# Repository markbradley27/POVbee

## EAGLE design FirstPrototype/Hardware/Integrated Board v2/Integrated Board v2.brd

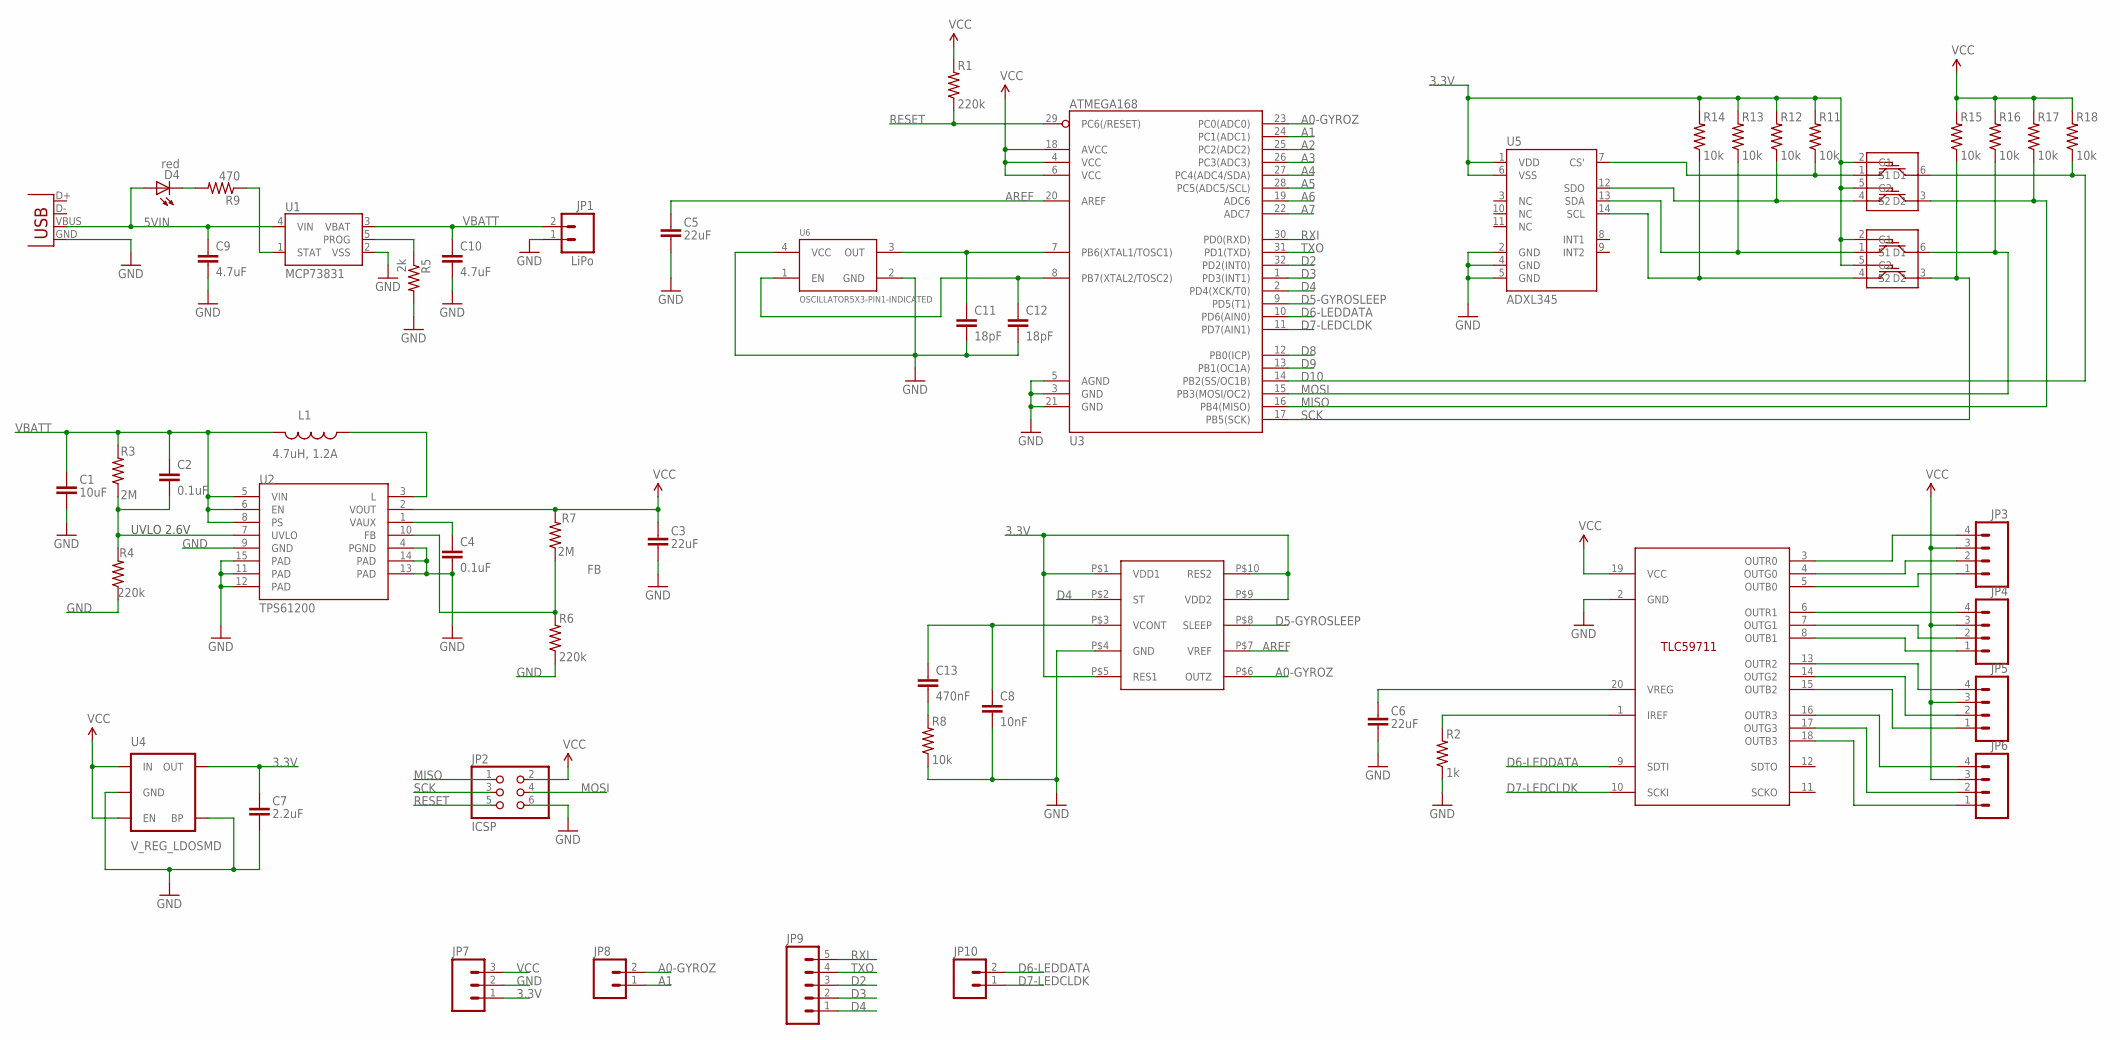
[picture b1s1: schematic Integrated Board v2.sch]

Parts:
C1: 10uF; 0603
C2, C4: 0.1uF; 0603-CAP
C3, C5, C6: 22uF; 0805
C7: 2.2uF; 0603
C8: 10nF; 0603-CAP
C9, C10: 4.7uF; 0603-CAP
C11, C12: 18pF; 0603-CAP
C13: 470nF; 0603-CAP
D4: red; LED-0603
JP1: LiPo; JST-2-SMD
JP2: ICSP; 2X03
JP3, JP4, JP5, JP6: M04PTH; 1X04
JP7: M03PTH; 1X03
JP8, JP10: M02PTH; 1X02
JP9: M05PTH; 1X05
L1: 4.7uH, 1.2A; CDRH2D09
R1, R4, R6: 220k; 0603-RES
R2: 1k; 0603-RES
R3, R7: 2M; 0603-RES
R5: 2k; 0603-RES
R8, R11, R12, R13, R14, R15, R16, R17, R18: 10k; 0603-RES
R9: 470; 0603-RES
U1: MCP73831; SOT23-5
U2: TPS61200; QFN-10_PAD
U3: ATMEGA168; TQFP32-08
U4: V_REG_LDOSMD; SOT23-5
U5: ADXL345; LGA14
U6: OSCILLATOR5X3-PIN1-INDICATED; CRYSTAL-OSC-SMD-5X3
U$1: TLC59711; TSSOP20
U$2, U$3: 2N7002DW; SOT363
U$4: LY3100ALH; LGA10
X1: USB-MICROB

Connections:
3.3V: C7.1, JP7.1, R11.2, R12.2, R13.2, R14.2, U4.5 (OUT), U5.1 (VDD), U5.6 (VSS), U$2.2 (G1), U$2.5 (G2), U$3.2 (G1), U$3.5 (G2), U$4.P$1 (VDD1), U$4.P$5 (RES1), U$4.P$9 (VDD2), U$4.P$10 (RES2)
5VIN: C9.1, D4.A, U1.4 (VIN), X1.VBUS
A0-GYROZ: JP8.2, U3.23 (PC0(ADC0)), U$4.P$6 (OUTZ)
A1: JP8.1, U3.24 (PC1(ADC1))
A2: U3.25 (PC2(ADC2))
A3: U3.26 (PC3(ADC3))
A4: U3.27 (PC4(ADC4/SDA))
A5: U3.28 (PC5(ADC5/SCL))
A6: U3.19 (ADC6)
A7: U3.22 (ADC7)
AREF: C5.1, U3.20 (AREF), U$4.P$7 (VREF)
D2: JP9.3, U3.32 (PD2(INT0))
D3: JP9.2, U3.1 (PD3(INT1))
D4: JP9.1, U3.2 (PD4(XCK/T0)), U$4.P$2 (ST)
D5-GYROSLEEP: U3.9 (PD5(T1)), U$4.P$8 (SLEEP)
D6-LEDDATA: JP10.2, U3.10 (PD6(AIN0)), U$1.9 (SDTI)
D7-LEDCLDK: JP10.1, U3.11 (PD7(AIN1)), U$1.10 (SCKI)
D8: U3.12 (PB0(ICP))
D9: U3.13 (PB1(OC1A))
D10: R18.1, U3.14 (PB2(SS/OC1B)), U$2.6 (D1)
FB: R6.2, R7.1, U2.10 (FB)
GND: C1.2, C3.2, C4.2, C5.2, C6.2, C7.2, C8.2, C9.2, C10.2, C11.2, C12.2, JP1.1, JP2.6, JP7.2, R2.1, R4.1, R5.2, R6.1, R8.1, U1.2 (VSS), U2.4 (PGND), U2.9 (GND), U2.11 (PAD), U2.12 (PAD), U2.13 (PAD), U2.14 (PAD), U2.15 (PAD), U3.3 (GND), U3.5 (AGND), U3.21 (GND), U4.2 (GND), U4.4 (BP), U5.2 (GND), U5.4 (GND), U5.5 (GND), U6.2 (GND), U6.4 (VCC), U$1.2 (GND), U$4.P$4 (GND), X1.GND
MISO: JP2.1, R17.1, U3.16 (PB4(MISO)), U$2.3 (D2)
MOSI: JP2.4, R16.1, U3.15 (PB3(MOSI/OC2)), U$3.6 (D1)
unnamed: C4.1, U2.1 (VAUX)
unnamed: L1.P$1 (1), U2.3 (L)
unnamed: C11.1, U3.7 (PB6(XTAL1/TOSC1)), U6.3 (OUT)
unnamed: C13.2, R8.2
unnamed: C6.1, U$1.20 (VREG)
unnamed: R2.2, U$1.1 (IREF)
unnamed: D4.C, R9.2
unnamed: R11.1, U5.7 (CS'), U$2.1 (S1)
unnamed: R5.1, U1.5 (PROG)
unnamed: R12.1, U5.12 (SDO), U$2.4 (S2)
unnamed: R13.1, U5.13 (SDA), U$3.1 (S1)
unnamed: R9.1, U1.1 (STAT)
unnamed: R14.1, U5.14 (SCL), U$3.4 (S2)
unnamed: JP4.4 (B), U$1.6 (OUTR1)
unnamed: JP4.2 (R), U$1.7 (OUTG1)
unnamed: JP4.1 (COM), U$1.8 (OUTB1)
unnamed: JP5.4 (B), U$1.13 (OUTR2)
unnamed: JP5.2 (R), U$1.14 (OUTG2)
unnamed: JP5.1 (COM), U$1.15 (OUTB2)
unnamed: JP6.4 (B), U$1.16 (OUTR3)
unnamed: JP6.2 (R), U$1.17 (OUTG3)
unnamed: JP6.1 (COM), U$1.18 (OUTB3)
unnamed: JP3.1 (COM), U$1.5 (OUTB0)
unnamed: JP3.2 (R), U$1.4 (OUTG0)
unnamed: JP3.4 (B), U$1.3 (OUTR0)
unnamed: C12.1, U3.8 (PB7(XTAL2/TOSC2)), U6.1 (EN)
unnamed: C8.1, C13.1, U$4.P$3 (VCONT)
RESET: JP2.5, R1.1, U3.29 (PC6(/RESET))
RXI: JP9.5, U3.30 (PD0(RXD))
SCK: JP2.3, R15.1, U3.17 (PB5(SCK)), U$3.3 (D2)
TXO: JP9.4, U3.31 (PD1(TXD))
UVLO: C2.2, R3.1, R4.2, U2.7 (UVLO)
VBATT: C1.1, C2.1, C10.1, JP1.2, L1.P$2 (2), R3.2, U1.3 (VBAT), U2.5 (VIN), U2.6 (EN), U2.8 (PS)
VCC: C3.1, JP2.2, JP3.3 (G), JP4.3 (G), JP5.3 (G), JP6.3 (G), JP7.3, R1.2, R7.2, R15.2, R16.2, R17.2, R18.2, U2.2 (VOUT), U3.4 (VCC), U3.6 (VCC), U3.18 (AVCC), U4.1 (IN), U4.3 (EN), U$1.19 (VCC)

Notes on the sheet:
UVLO 2.6V

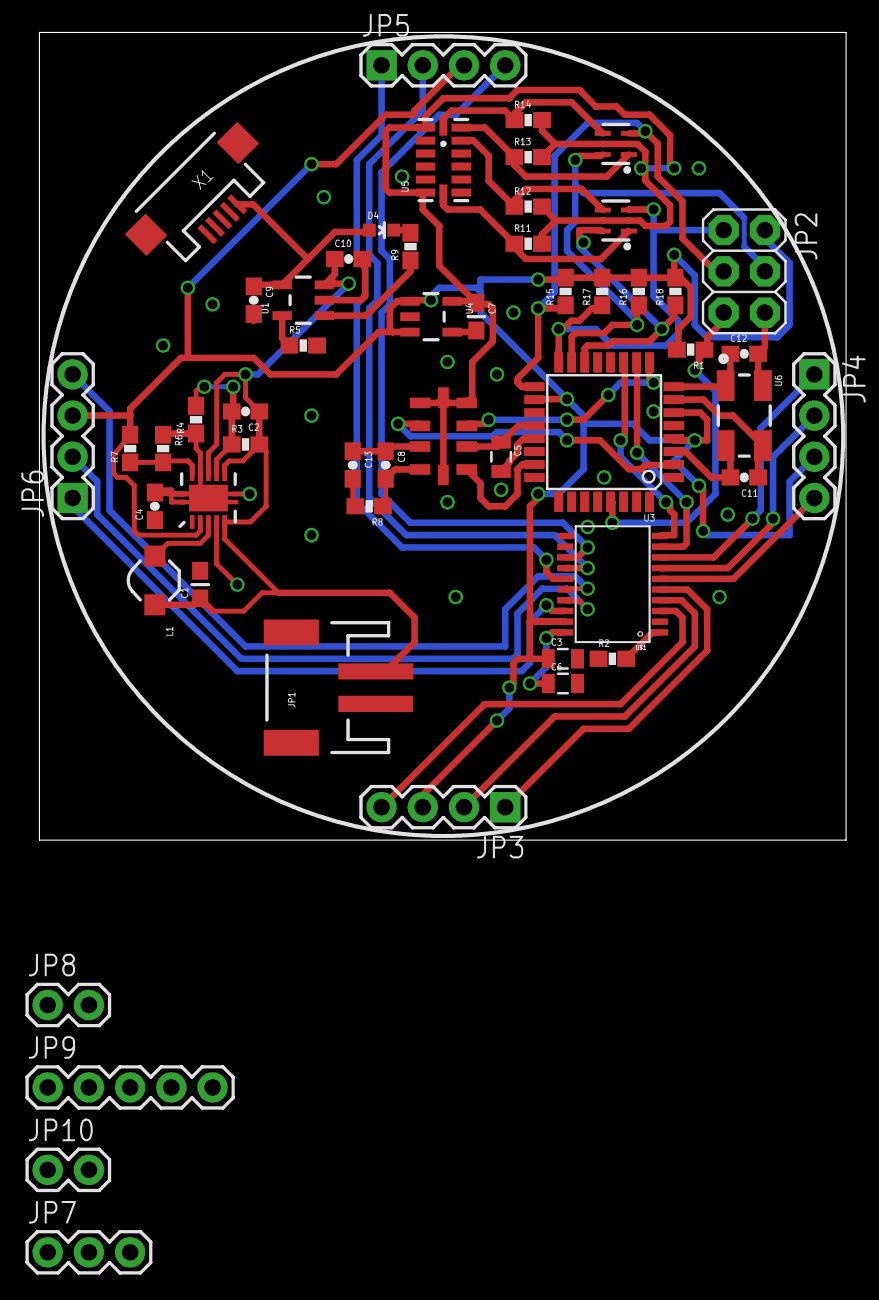
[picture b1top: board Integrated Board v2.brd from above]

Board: 2 copper layers, 49.7 x 49.8 mm, 53 parts (0 on the bottom side), 50 nets.

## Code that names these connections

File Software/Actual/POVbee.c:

/********************************************************************************
Includes
********************************************************************************/
#include <avr/io.h>
#include <avr/interrupt.h>
#include <stdbool.h>
#include <avr/eeprom.h>
#include <stdio.h>
#include <string.h>
#include <avr/pgmspace.h>
#include <avr/interrupt.h>
#include "WS2811.h"
 
/********************************************************************************
Macros and Defines
********************************************************************************/
#define F_CPU 16000000UL
#define BAUD 9600UL
#define MYUBRR F_CPU/16/BAUD-1
DEFINE_WS2811_FN(WS2811RGB, PORTC, 2)
 
/********************************************************************************
Function Prototypes
********************************************************************************/
int16_t get_rotation_gyro(void);
void accel_init(void);
int16_t accel_read_axis(uint8_t);
void port_init(void);
void adc_init(void);
void spim_init(void);
void timer_init(void);
void spi_tx(char data);
uint16_t analog_read(uint8_t channel);
void usart_init( uint16_t ubrr);
void usart_putchar(char data);
char usart_getchar(void);
unsigned char usart_kbhit(void);
void usart_pstr(char *s);
int usart_putchar_printf(char var, FILE *stream);

/********************************************************************************
Global Variables
********************************************************************************/
static FILE mystdout = FDEV_SETUP_STREAM(usart_putchar_printf, NULL, _FDEV_SETUP_WRITE);
RGB_t rgb[4] = {{0, 0, 0}, {0, 0, 0}, {0, 0, 0}, {0, 0, 0}};
uint32_t milis = 0;

/********************************************************************************
Main
********************************************************************************/
int main(void) {
    // AVR init
    port_init();
    adc_init();
    spim_init();
    usart_init(MYUBRR);
    timer_init();
    sei();              // Enable interrupts
    stdout = &mystdout;

    // Device init
    accel_init();

    // Variable declaration
    int16_t rotation = 0;
    int16_t accel_x = 0;
    int16_t accel_y = 0;
    int16_t accel_z = 0;
    uint8_t seconds = 0;

    // Main loop
    while (true) {
        rotation = get_rotation_gyro();
        accel_x = accel_read_axis('x');
        accel_y = accel_read_axis('y');
        accel_z = accel_read_axis('z');

        // Roughly estimate seconds
        if (milis >= 1000) {
            ++seconds;
            milis = 0;
        }

        printf("Rotation: %3d\t", rotation);
        printf("Accel: %3d,\t%3d,\t%3d\t", accel_x, accel_y, accel_z);
        printf("Seconds: %3u\r\n", seconds);

        uint8_t i;
        if (rotation < -15) {
            for (i = 0; i < 4; ++i) {
                rgb[i].g = 255;
                rgb[i].b = 0;
                rgb[i].r = 0;
            }
        }
        else if (rotation > 15) {
            for (i = 0; i < 4; ++i) {
                rgb[i].g = 0;
                rgb[i].b = 255;
                rgb[i].r = 0;
            }
        }
        else {
            for (i = 0; i < 4; ++i) {
                rgb[i].g = 0;
                rgb[i].b = 0;
                rgb[i].r = 255;
            }
        }

        WS2811RGB(rgb, ARRAYLEN(rgb));
    }
}

/********************************************************************************
Device helpers
********************************************************************************/
// Gyro
int16_t get_rotation_gyro(void) {
    return analog_read(7) - analog_read(6);
}

// Accel
void accel_init(void) {
    // Set to standby mode
    PORTB &= ~(1<<PB2);
    spi_tx(0x2D);
    spi_tx(0x00);
    PORTB |= (1<<PB2);

    // Set to measure mode
    PORTB &= ~(1<<PB2);
    spi_tx(0x2D);
    spi_tx(0x08);
    PORTB |= (1<<PB2);

    // Set to +/- 16g, full-resolution
    PORTB &= ~(1<<PB2);
    spi_tx(0x31);
    spi_tx(0x0B);
    PORTB |= (1<<PB2);
}
int16_t accel_read_axis(uint8_t axis) {
    int16_t axis_accel = 0x00;
    switch(axis) {
        case 'x': axis = 0x32; break;
        case 'y': axis = 0x34; break;
        case 'z': axis = 0x36; break;
        default: return 0;
    }

    // Pull CS low
    PORTB &= ~(1<<PB2);

    // Read x data registers
    spi_tx(0x80 | 0x40 | axis);
    spi_tx(0x00);
    axis_accel |= SPDR;
    spi_tx(0x00);
    axis_accel |= SPDR << 8;

    // Drive CS high
    PORTB |= (1<<PB2);

    return axis_accel;
}

// Timer
uint32_t get_micros(void) {
    return (milis * 1000) + ((uint32_t)(TCNT0 - 6) * 4);
}
void timer_reset(void) {
    TCNT0 = 6;
    milis = 0;
}

/********************************************************************************
Device initialization
********************************************************************************/
void port_init(void) {
    // Turn on green light
    PORTC &= ~(1 << PC4);
    DDRC |= (1 << PC4);

    // Gyro pins
    PORTC &= ~(1 << PC0);
    PORTC &= ~(1 << PC1);
    DDRC |= 0x03;

    // Pixel pin
    DDRC |= (1<<PC2);
    PORTC &= ~(1<<PC2);
}

void adc_init(void) {
    ADMUX &= ~0xE0;         // AREF reference voltage, right adjusted result
    ADCSRA = 0x87;          // ADC enabled, no auto-trigger, aclock = sysclock/128
}

void spim_init(void) {
    DDRB = (1<<PB2)|(1<<PB3)|(1<<PB5);     // Set CS, MOSI, and SCK output, all others input
    PORTB |= (1<<PB2);                     // Set CS high initially
    // TODO: Try speeding this back up
    SPCR = (1<<SPE)|(1<<MSTR)|(1<<CPOL)|(1<<CPHA)|(1<<SPR1)|(1<<SPR0);    // Enable SPI, Master, set clock rate fck/128
}

void timer_init(void) {
    TIMSK0 = (1<<TOIE0);            // Enable timer overflow interrupt for timer0
    TCNT0 = 0x00;                   // Set timer0 counter initial value to 0
    TCCR0B = (1<<CS00)|(1<<CS01);   // Start timer0 with 1/64 prescaler
}

/********************************************************************************
Interrupt Service Routines
********************************************************************************/
ISR(TIMER0_OVF_vect) {
    ++milis;
    TCNT0 = 6;
}

/********************************************************************************
ADC Related
********************************************************************************/
uint16_t analog_read(uint8_t channel) {
    ADMUX = (ADMUX & 0xF0) | channel;
    ADCSRA |= 0x40;
    while(!(ADCSRA & 0x10));
    ADCSRA |= 0x10;
    return ADC;
}

/********************************************************************************
SPI Related
********************************************************************************/
void spi_tx(char data) {
    SPDR = data;
    while(!(SPSR & (1<<SPIF)));
}

/********************************************************************************
usart Related
********************************************************************************/
void usart_init( uint16_t ubrr) {
    // Set baud rate
    UBRR0H = (uint8_t)(ubrr>>8);
    UBRR0L = (uint8_t)ubrr;
    // Enable receiver and transmitter
    UCSR0B = (1<<RXEN0)|(1<<TXEN0);
    // Set frame format: 8data, 1stop bit
    //UCSR0C = (1<<URSEL)|(3<<UCSZ0);
    UCSR0C = (3<<UCSZ00);
}
void usart_putchar(char data) {
    // Wait for empty transmit buffer
    while ( !(UCSR0A & (_BV(UDRE0))) );
    // Start transmission
    UDR0 = data; 
}
char usart_getchar(void) {
    // Wait for incoming data
    while ( !(UCSR0A & (_BV(RXC0))) );
    // Return the data
    return UDR0;
}
unsigned char usart_kbhit(void) {
    //return nonzero if char waiting polled version
    unsigned char b;
    b=0;
    if(UCSR0A & (1<<RXC0)) b=1;
    return b;
}
void usart_pstr(char *s) {
    // loop through entire string
    while (*s) { 
        usart_putchar(*s);
        s++;
    }
}
int usart_putchar_printf(char var, FILE *stream) {
    usart_putchar(var);
    return 0;
}

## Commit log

2014-11-14 Added old files
2014-11-14 Moved things around, have printf working, rough build routine
2014-11-14 Added datasheets
2014-11-14 Moar datasheets\!
2014-11-14 Added analog read
2014-11-14 Added gyro get-rotation helper
2014-11-15 Accelerometer works\!
2014-11-18 Accelerometer tweaks
2014-11-18 Added next-rev board notes
2014-11-18 gitignore Thumbs.db
2014-11-18 Pixels work
2014-11-18 Rearranged accelerometer read functions
2014-11-25 LEDs work\!
2014-11-28 Added timer, helper functions for reading every 4 microseconds
